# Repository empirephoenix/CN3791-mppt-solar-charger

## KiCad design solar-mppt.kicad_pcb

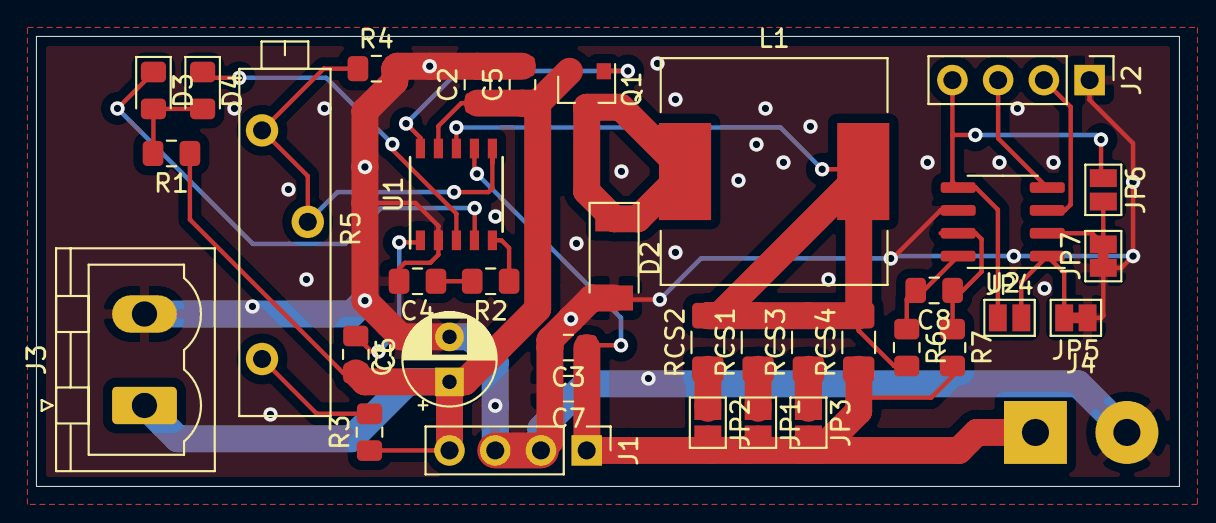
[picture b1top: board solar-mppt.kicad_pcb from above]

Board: 2 copper layers, 63.5 x 25.0 mm, 37 parts (0 on the bottom side), 24 nets.

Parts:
C1: CP; CP_Radial_D5.0mm_P2.50mm
C2, C3: 1-10uF; C_0805_2012Metric_Pad1.15x1.40mm_HandSolder
C4: 0.22uF; C_0805_2012Metric_Pad1.15x1.40mm_HandSolder
C5: 1-47nf; C_0805_2012Metric_Pad1.15x1.40mm_HandSolder
C6, C8: 0.1uF; C_0805_2012Metric_Pad1.15x1.40mm_HandSolder
C7: 10uF; C_0805_2012Metric_Pad1.15x1.40mm_HandSolder
D2: D_Schottky; D_SOD-128
D3, D4: LED; LED_0805_2012Metric_Pad1.15x1.40mm_HandSolder
J1, J2: Conn_01x04_Female; PinHeader_1x04_P2.54mm_Vertical
J3: Conn_01x02_Female; PhoenixContact_MSTBVA_2,5_2-G-5,08_1x02_P5.08mm_Vertical
J4: Conn_01x02_Female; SolderWirePad_1x02_P5.08mm_Drill1.5mm
JP1, JP2, JP3, JP4, JP6: SolderJumper_2_Open; SolderJumper-2_P1.3mm_Open_Pad1.0x1.5mm
JP5, JP7: SolderJumper_2_Bridged; SolderJumper-2_P1.3mm_Bridged_Pad1.0x1.5mm
L1: >70uH > 4A; L_12x12mm_H8mm
Q1: AO3401A; SOT-23
R1: 1K; R_0805_2012Metric_Pad1.15x1.40mm_HandSolder
R2: 120; R_0805_2012Metric_Pad1.15x1.40mm_HandSolder
R3: 40K; R_0805_2012Metric_Pad1.15x1.40mm_HandSolder
R4: 10K; R_0805_2012Metric_Pad1.15x1.40mm_HandSolder
R5: 100K; Potentiometer_Bourns_3006P_Horizontal
R6, R7: 10; R_0805_2012Metric_Pad1.15x1.40mm_HandSolder
RCS1, RCS2, RCS3, RCS4: 0.12; R_1206_3216Metric_Pad1.42x1.75mm_HandSolder
U1: CN3791; SSOP-10_3.9x4.9mm_P1.00mm
U2: INA219AxD; SOIC-8_3.9x4.9mm_P1.27mm

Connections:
BAT: C3.1, C7.1, J1.1, J4.1, JP1.2, JP2.2, JP3.2, R7.2, RCS4.1, U1.7
GND: C1.2, C2.2, C3.2, C4.2, C5.2, C7.2, D2.2, J1.2, J1.3, J2.1, J3.2, J4.2, JP5.1, JP7.1, R4.2, U1.2, U2.6
unnamed: C4.1, R2.2
unnamed: C6.1, U1.1
unnamed: C8.1, R7.1, U2.7
unnamed: C8.2, R6.1, U2.8
unnamed: D2.1, L1.1, Q1.3
unnamed: D3.1, U1.4
unnamed: D3.2, D4.2, R1.2
unnamed: D4.1, U1.3
unnamed: J2.2, U2.3
unnamed: J2.3, U2.4
unnamed: JP1.1, RCS1.1
unnamed: JP2.1, RCS2.1
unnamed: JP3.1, RCS3.1
unnamed: JP4.2, JP5.2, U2.1
unnamed: JP6.2, JP7.2, U2.2
unnamed: L1.2, R6.2, RCS1.2, RCS2.2, RCS3.2, RCS4.2, U1.8
unnamed: Q1.1, U1.10
unnamed: R2.1, U1.5
unnamed: R3.2, R5.1
unnamed: R4.1, R5.2, R5.3, U1.6
SOLAR_IN: C1.1, C2.1, C5.1, C6.2, J1.4, J3.1, Q1.2, R1.1, R3.1, U1.9
V_Sensor: J2.4, JP4.1, JP6.1, U2.5

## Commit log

2021-02-15 initial version
